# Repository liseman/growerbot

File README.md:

# Growerbot

Welcome to the Growerbot github repository. The growerbot is a social gardening assistant, more details at [growerbot.com](http://www.growerbot.com/)

## Arduino source 

To use the Arduino source you'll need those three libraries :

* [Time Library](http://www.arduino.cc/playground/uploads/Code/Time.zip)
* [Adafruits Lux sensor library](https://github.com/adafruit/TSL2561-Arduino-Library)
* [Adafruits DHT sensor library](https://github.com/adafruit/DHT-sensor-library)

Download them and put them into the libraries folder of your Aduino IDE installation.

To install Arduino IDE please go to : [http://arduino.cc/en/Main/Software](http://arduino.cc/en/Main/Software)

To upload the program into the Growerbot please follow the instruction on the fifth video of the [assembly videos](http://www.growerbot.com/2013/02/03/growerbot-kit-assembly-videos/).

### Linux Users

If you have installed Arduino IDE via an installer (i.e. apt-get) note that your library may be in your home folder at ~/sketchbook/libraries (Tested only with Ubuntu).
Also if you have problems compiling the Time library and it's the Time/DateString.cpp file that cause the problem you can remove all the "PROGMEM" keywords to make it compile without problems.

## Electric Imp Source

Those file are samples to use with the Electrc Imp SD card. Please refer to the Readme file into the folder for more help.

## PCBs

Those are the schematics and board design to build a Growerbot, you can also buy a kit at [www.growerbot.com/buy/](http://www.growerbot.com/buy/).

To learn what you need and how to build your Growerbot please watch the assembly videos at [www.growerbot.com/blog/](http://www.growerbot.com/2013/02/03/growerbot-kit-assembly-videos/)

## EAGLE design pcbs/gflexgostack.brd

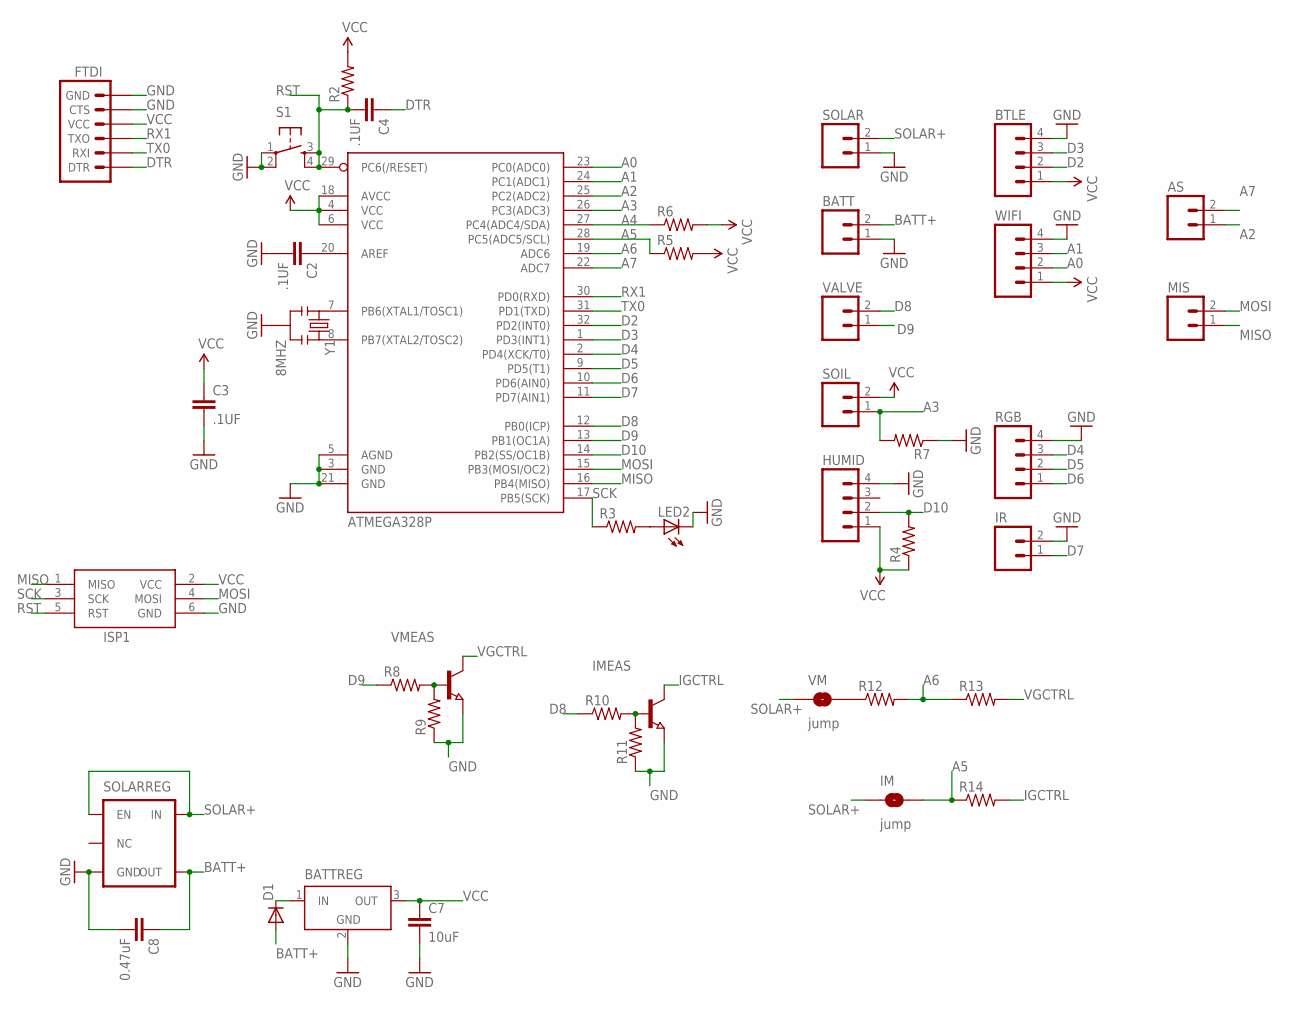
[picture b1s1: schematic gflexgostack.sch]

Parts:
AS: M02PTH; 1X02; DIGI PPTC021LFBN-RC
ATMEGA328P: ATMEGA168; TQFP32-08; DIGI ATMEGA328P-AU
BATT: M02PTH; 1X02; DIGI PPTC021LFBN-RC
BATTREG: LT1129CST5; SOT223; MPN LT1129CST-3.3#PBF-ND; DIGI MCP1826S-3302E/DB
BTLE: M04PTH; 1X04; DIGI PPTC041LFBN-RC
C2, C3, C4: .1UF; 0402-CAP; DIGI GRM155R71C104KA88D
C7: 10uF; 0402-CAP; DIGI AMK105CBJ106MV-F
C8: 0.47uF; 0402-CAP; DIGI GRM155R61A474KE15D
D1: DIODESMA; SMA-DIODE; DIGI B340A-13-F
FTDI: ARDUINO_SERIAL_PROGRAMPTH; 1X06; DIGI PPTC061LFBN-RC
HUMID: M04PTH; 1X04; DIGI PPTC041LFBN-RC
IM: jump; SJ_2S-TRACE
IMEAS: NPN-TRANSISTOR_SOT23; SOT23
IR: M02PTH; 1X02; DIGI PPTC021LFBN-RC
ISP1: AVRISP-6; AVRISP; DIGI 961206-6404-AR
LED2: LED0603; LED-0603; DIGI TLMG1100-GS08
MIS: M02PTH; 1X02; DIGI PPTC021LFBN-RC
R2, R4, R5, R6, R7: RESISTOR0603-RES; 0603-RES; DIGI ERJ-3GEYJ103V
R3: RESISTOR0603-RES; 0603-RES; DIGI ERJ-3GEYJ331V
R8, R10: RESISTOR0603-RES; 0603-RES; DIGI ERJ-3GEYJ431V
R9, R11: RESISTOR0603-RES; 0603-RES; DIGI ERJ-3GEYJ432V
R12: RESISTOR0603-RES; 0603-RES; DIGI ERJ-3GEYJ202V
R13: RESISTOR0603-RES; 0603-RES; DIGI ERJ-3GEYJ102V
R14: RESISTOR0603-RES; 0603-RES; DIGI ERJ-3RSJR10V
RGB: M04PTH; 1X04; DIGI PPTC041LFBN-RC
S1: TAC_SWITCHSMD; TACTILE_SWITCH_SMD; DIGI RS-187R05A2-DS MT RT
SOIL: M02PTH; 1X02; DIGI PPTC021LFBN-RC
SOLAR: M02PTH; 1X02; DIGI PPTC021LFBN-RC
SOLARREG: V_REG_MIC52195V; SOT23-5; DIGI MIC5213-5.0YC5 TR
VALVE: M02PTH; 1X02; DIGI PPTC021LFBN-RC
VM: jump; SJ_2S-TRACE
VMEAS: NPN-TRANSISTOR_SOT23; SOT23
WIFI: M04PTH; 1X04; DIGI PPTC041LFBN-RC
Y1: 8MHZ; RESONATOR-SMD; DIGI PRQV8.00CR5010Y000

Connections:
A0: ATMEGA328P.23 (PC0(ADC0)), WIFI.2
A1: ATMEGA328P.24 (PC1(ADC1)), WIFI.3
A2: AS.1, ATMEGA328P.25 (PC2(ADC2))
A3: ATMEGA328P.26 (PC3(ADC3)), R7.2, SOIL.1
A4: ATMEGA328P.27 (PC4(ADC4/SDA)), R6.1
A5: ATMEGA328P.28 (PC5(ADC5/SCL)), IM.2, R5.1, R14.1
A6: ATMEGA328P.19 (ADC6), R12.2, R13.1
A7: AS.2, ATMEGA328P.22 (ADC7)
BATT+: BATT.2, C8.1, D1.A, SOLARREG.4 (OUT)
D2: ATMEGA328P.32 (PD2(INT0)), BTLE.2
D3: ATMEGA328P.1 (PD3(INT1)), BTLE.3
D4: ATMEGA328P.2 (PD4(XCK/T0)), RGB.3
D5: ATMEGA328P.9 (PD5(T1)), RGB.2
D6: ATMEGA328P.10 (PD6(AIN0)), RGB.1
D7: ATMEGA328P.11 (PD7(AIN1)), IR.1
D8: ATMEGA328P.12 (PB0(ICP)), R10.1, VALVE.2
D9: ATMEGA328P.13 (PB1(OC1A)), R8.1, VALVE.1
D10: ATMEGA328P.14 (PB2(SS/OC1B)), HUMID.2, R4.2
DTR: C4.1, FTDI.1 (DTR)
GND: ATMEGA328P.3 (GND), ATMEGA328P.5 (AGND), ATMEGA328P.21 (GND), BATT.1, BATTREG.2 (GND), BATTREG.4 (GND), BTLE.4, C2.2, C3.2, C7.2, C8.2, FTDI.5 (CTS), FTDI.6 (GND), HUMID.4, IMEAS.2 (E), IR.2, ISP1.6 (GND), LED2.C, R7.1, R9.1, R11.1, RGB.4, S1.1, S1.2, SOLAR.1, SOLARREG.3 (GND), VMEAS.2 (E), WIFI.4, Y1.2
IGCTRL: IMEAS.3 (C), R14.2
MISO: ATMEGA328P.16 (PB4(MISO)), ISP1.1 (MISO), MIS.1
MOSI: ATMEGA328P.15 (PB3(MOSI/OC2)), ISP1.4 (MOSI), MIS.2
unnamed: ATMEGA328P.8 (PB7(XTAL2/TOSC2)), Y1.3
unnamed: ATMEGA328P.7 (PB6(XTAL1/TOSC1)), Y1.1
unnamed: R8.2, R9.2, VMEAS.1 (B)
unnamed: ATMEGA328P.20 (AREF), C2.1
unnamed: LED2.A, R3.2
unnamed: IMEAS.1 (B), R10.2, R11.2
unnamed: R12.1, VM.2
unnamed: BATTREG.1 (IN), D1.C
RST: ATMEGA328P.29 (PC6(/RESET)), C4.2, ISP1.5 (RST), R2.1, S1.3, S1.4
RX1: ATMEGA328P.30 (PD0(RXD)), FTDI.3 (TXO)
SCK: ATMEGA328P.17 (PB5(SCK)), ISP1.3 (SCK), R3.1
SOLAR+: IM.1, SOLAR.2, SOLARREG.1 (EN), SOLARREG.5 (IN), VM.1
TX0: ATMEGA328P.31 (PD1(TXD)), FTDI.2 (RXI)
VCC: ATMEGA328P.4 (VCC), ATMEGA328P.6 (VCC), ATMEGA328P.18 (AVCC), BATTREG.3 (OUT), BTLE.1, C3.1, C7.1, FTDI.4 (VCC), HUMID.1, ISP1.2 (VCC), R2.2, R4.1, R5.2, R6.2, SOIL.2, WIFI.1
VGCTRL: R13.2, VMEAS.3 (C)

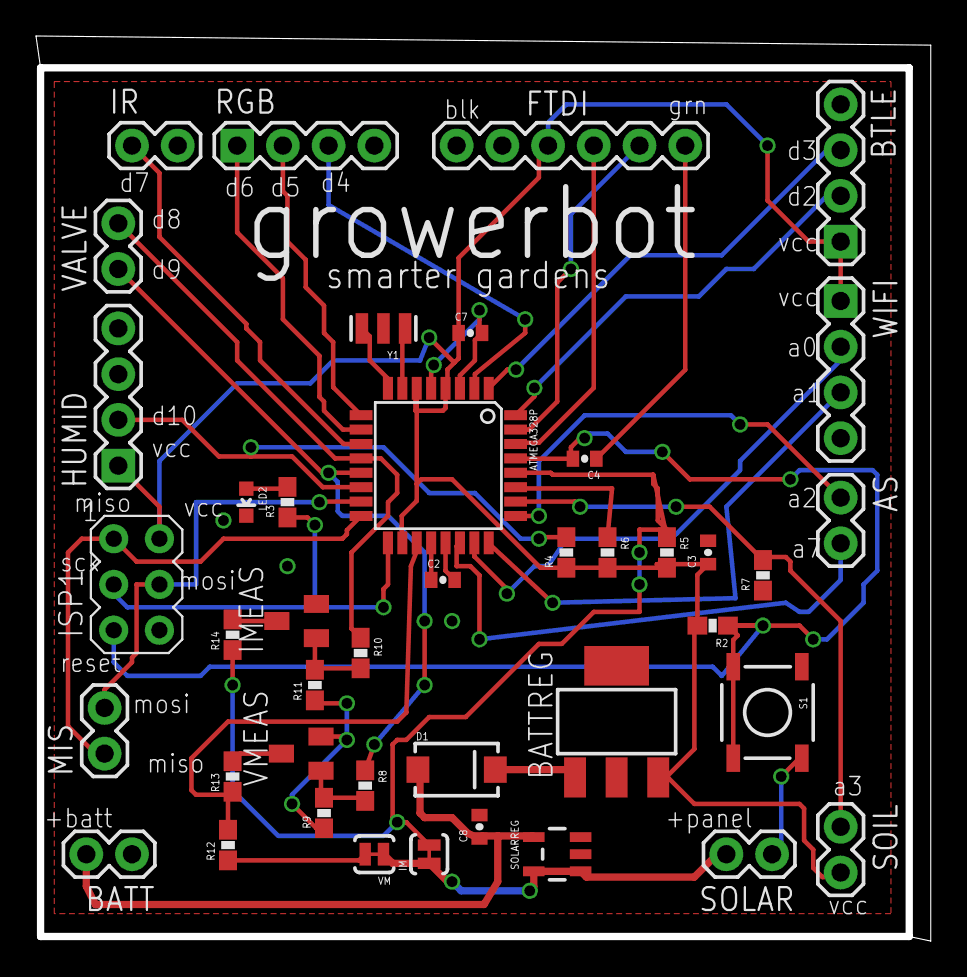
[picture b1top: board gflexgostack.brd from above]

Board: 4 copper layers, 49.3 x 49.9 mm, 43 parts (0 on the bottom side), 38 nets.

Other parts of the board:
U$1: GLOGO

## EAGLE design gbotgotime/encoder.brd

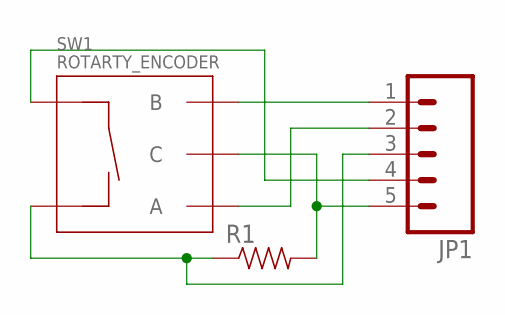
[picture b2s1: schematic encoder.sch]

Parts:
JP1: M05PTH; 1X05
R1: RESISTORPTH-1/4W; AXIAL-0.4
SW1: ROTARTY_ENCODER; ROTARY_ENC_PLAIN

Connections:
unnamed: JP1.1, SW1.B
unnamed: JP1.2, SW1.A
unnamed: JP1.5, R1.P$2 (2), SW1.C
unnamed: JP1.3, R1.P$1 (1), SW1.SW-
unnamed: JP1.4, SW1.SW+

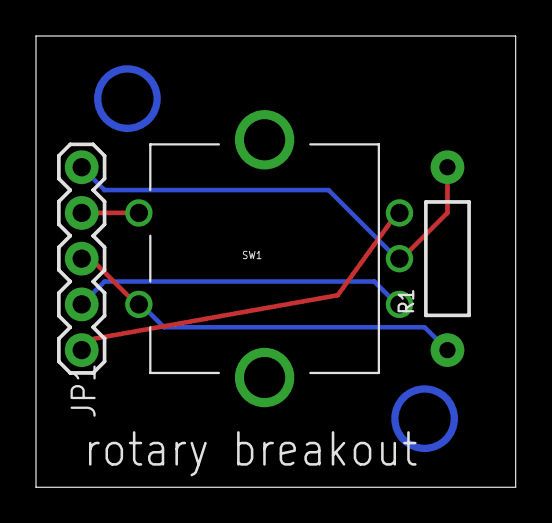
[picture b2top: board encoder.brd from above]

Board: 2 copper layers, 26.6 x 25.1 mm, 3 parts (0 on the bottom side), 5 nets.

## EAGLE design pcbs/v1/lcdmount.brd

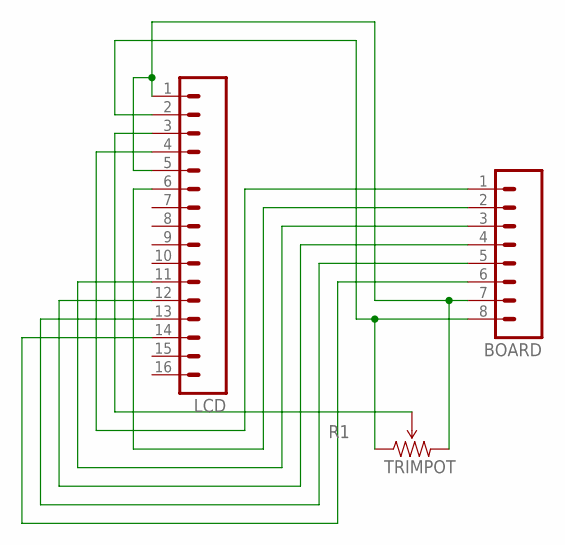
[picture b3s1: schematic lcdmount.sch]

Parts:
BOARD: M081X08; 1X08
LCD: M16PTH; 1X16
R1: TRIMPOT; 3362U-2

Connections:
unnamed: BOARD.7, LCD.1, LCD.5, R1.3 (CW)
unnamed: BOARD.8, LCD.2, R1.1 (CCW)
unnamed: LCD.3, R1.2 (WIPER)
unnamed: BOARD.1, LCD.4
unnamed: BOARD.3, LCD.11
unnamed: BOARD.2, LCD.6
unnamed: BOARD.4, LCD.12
unnamed: BOARD.5, LCD.13
unnamed: BOARD.6, LCD.14

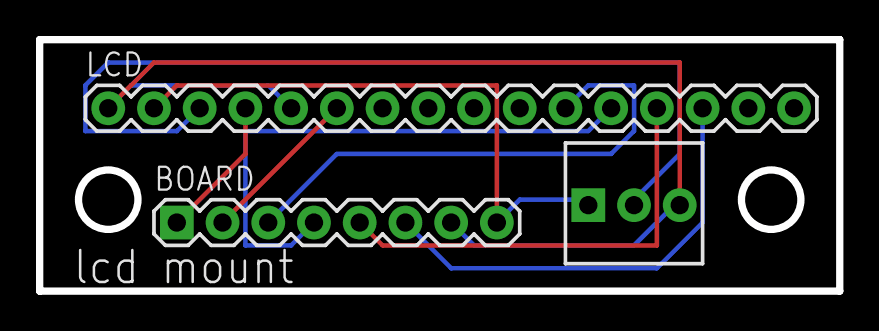
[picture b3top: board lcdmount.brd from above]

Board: 2 copper layers, 44.5 x 14.0 mm, 3 parts (0 on the bottom side), 9 nets.

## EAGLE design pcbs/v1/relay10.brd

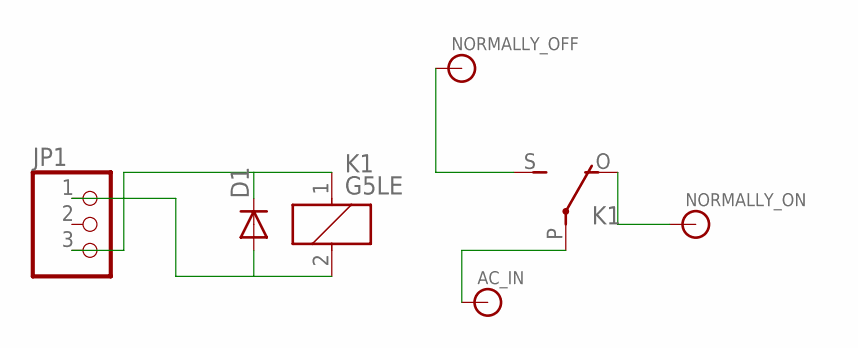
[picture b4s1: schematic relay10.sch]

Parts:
AC_IN: BANANA_CONN
D1: 1N4004; DO41-10
JP1: PINHD-1X3; 1X03
K1: G5LE
NORMALLY_OFF: BANANA_CONN
NORMALLY_ON: BANANA_CONN

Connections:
unnamed: D1.A, JP1.1, K1.2
unnamed: D1.C, JP1.3, K1.1
unnamed: K1.S, NORMALLY_OFF.P$1
unnamed: K1.O, NORMALLY_ON.P$1
unnamed: AC_IN.P$1, K1.P

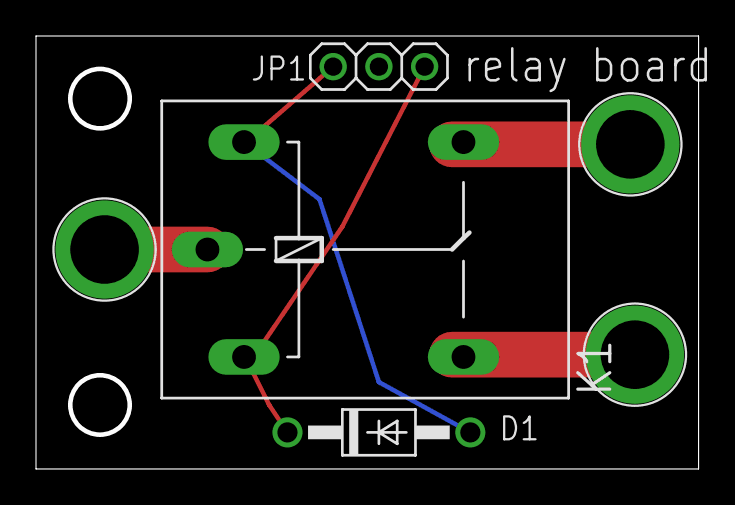
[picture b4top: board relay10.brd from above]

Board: 2 copper layers, 36.6 x 23.8 mm, 6 parts (0 on the bottom side), 5 nets.

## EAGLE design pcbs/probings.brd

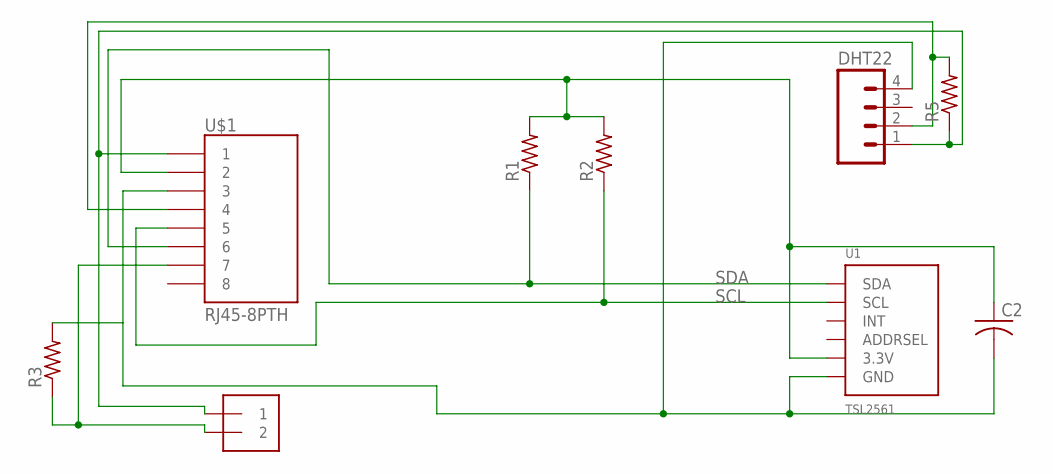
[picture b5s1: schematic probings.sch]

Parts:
C2: C-US025-024X044; C025-024X044
DHT22: M04PTH; 1X04
J1: 1X2-3.5MM
R1, R2, R3, R5: R-US_0204/7; 0204/7
U1: TSL2561; TSL2561_FN
U$1: RJ45-8PTH; RJ45-8

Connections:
unnamed: C2.1, R1.2, R2.2, U1.VDD (3.3V), U$1.2
unnamed: C2.2, DHT22.4, R3.2, U1.VSS (GND), U$1.3
unnamed: DHT22.1, J1.1, R5.1, U$1.1
unnamed: DHT22.2, R5.2, U$1.4
unnamed: J1.2, R3.1, U$1.7
SCL: R2.1, U1.CLK (SCL), U$1.5
SDA: R1.1, U1.DATA (SDA), U$1.6

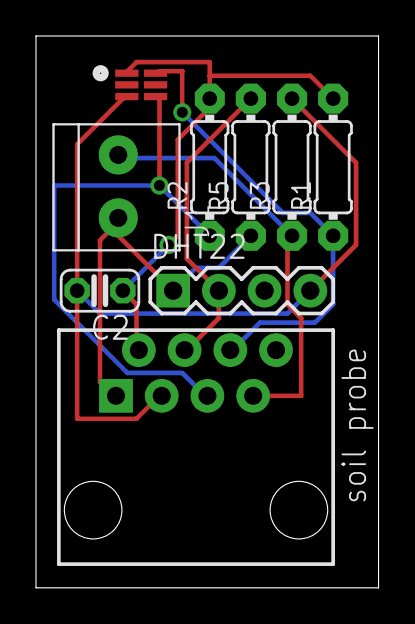
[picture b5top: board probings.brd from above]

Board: 2 copper layers, 19.0 x 30.7 mm, 9 parts (0 on the bottom side), 7 nets.

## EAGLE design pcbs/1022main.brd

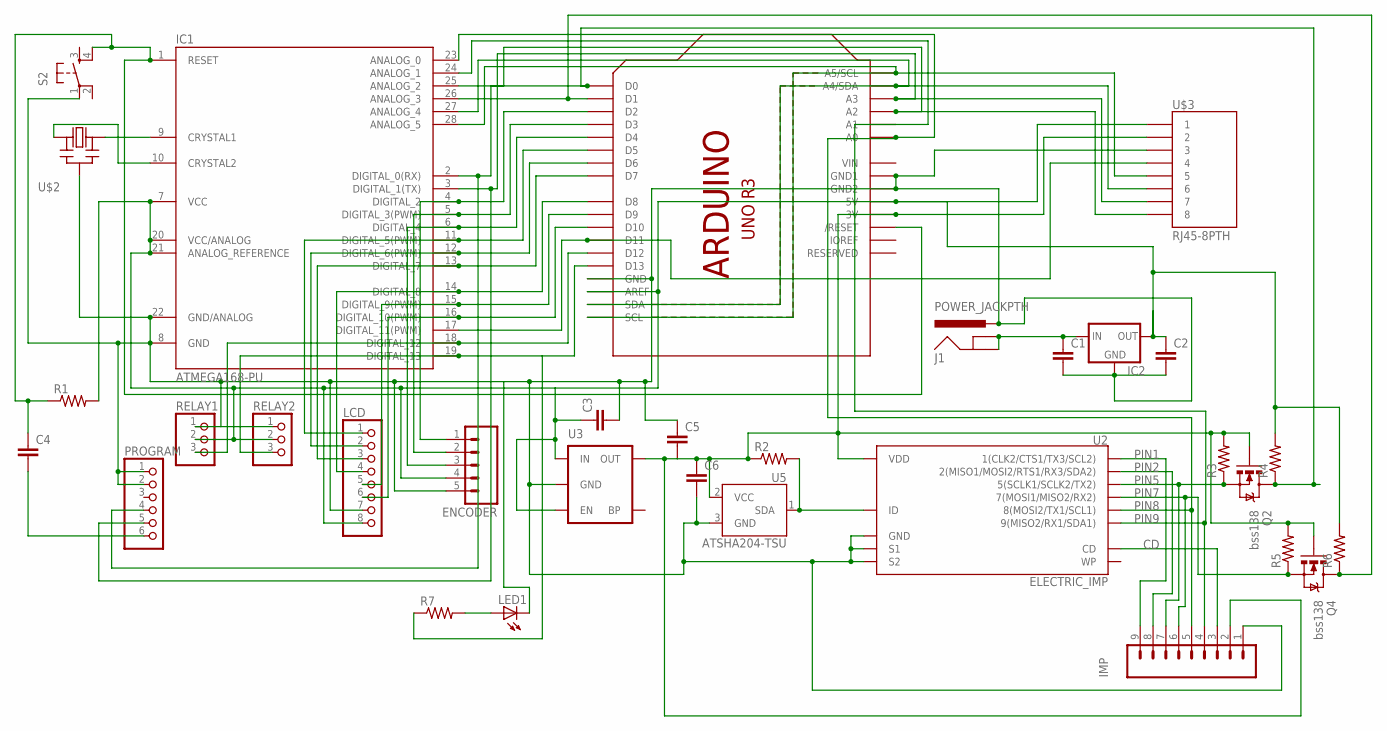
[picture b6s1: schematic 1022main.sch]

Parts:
C1, C2, C3, C4, C5, C6: CAPPTH; CAP-PTH-SMALL
ENCODER: M05PTH; 1X05
IC1: ATMEGA168-PU; DIL28-3
IC2: V_REG_78XX-TO-220; TO-220-ALT
IMP: M09; 1X09
J1: POWER_JACKPTH; POWER_JACK_PTH
LCD: PINHD-1X8CLEANBIG; 1X08-CLEANBIG
LED1: LED3MM
PROGRAM: PINHD-1X6; 1X06
Q2, Q4: bss138; SOT23-3
R1, R2, R3, R4, R5, R6, R7: R-US_0204/7; 0204/7
RELAY1, RELAY2: PINHD-1X3; 1X03
S2: TAC_SWITCHPTH; TACTILE-PTH
U1: ARDUINOR3-DIMENSION; ARDUINOR3
U2: ELECTRIC_IMP; SD_MMC_SOCKET
U3: V_REG_MIC52193.3V; SOT23-5
U5: ATSHA204-TSU; SOT23-3
U$2: CERMOSCILL-THM; CERM_OSC
U$3: RJ45-8PTH; RJ45-8

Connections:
3.3V: C5.2, C6.1, IMP.2, Q2.1 (G), Q4.1 (G), R2.1, R3.2, R5.2, U1.3V, U2.4 (VDD), U3.5 (OUT), U5.2 (VCC), U$3.2
CD: IMP.3, U2.CD
GND: C1.2, C2.2, C3.2, C5.1, C6.2, ENCODER.5, IC1.8 (GND), IC1.22 (GND/ANALOG), IC2.GND, IMP.1, J1.PWR, LCD.7, LED1.K (C), PROGRAM.1, PROGRAM.2, RELAY1.1, RELAY2.1, S2.1, U1.GND, U1.GND1, U1.GND2, U2.3 (GND), U2.S1, U2.S2, U3.2 (GND), U5.3 (GND), U$2.P$2 (GND), U$3.3
unnamed: IC1.19 (DIGITAL_13), R7.1, RELAY2.3, U1.D13
unnamed: IC1.18 (DIGITAL_12), RELAY1.3, U1.D12
unnamed: IC1.17 (DIGITAL_11(PWM)), U1.D11, U$3.4
unnamed: IC1.16 (DIGITAL_10(PWM)), LCD.6, U1.D10
unnamed: IC1.15 (DIGITAL_9(PWM)), LCD.5, U1.D9
unnamed: IC1.14 (DIGITAL_8), LCD.4, U1.D8
unnamed: IC1.13 (DIGITAL_7), LCD.3, U1.D7
unnamed: IC1.12 (DIGITAL_6(PWM)), LCD.2, U1.D6
unnamed: IC1.11 (DIGITAL_5(PWM)), LCD.1, U1.D5
unnamed: ENCODER.3, IC1.6 (DIGITAL_4), U1.D4
unnamed: ENCODER.2, IC1.5 (DIGITAL_3(PWM)), U1.D3
unnamed: ENCODER.1, IC1.4 (DIGITAL_2), U1.D2
unnamed: IC1.3 (DIGITAL_1(TX)), PROGRAM.5, Q4.3 (D), R6.1, U1.D1
unnamed: IC1.2 (DIGITAL_0(RX)), PROGRAM.4, Q2.3 (D), R4.1, U1.D0
unnamed: IC1.27 (ANALOG_4), U1.A4 (A4/SDA), U1.SDA, U$3.6
unnamed: IC1.28 (ANALOG_5), U1.A5 (A5/SCL), U1.SCL, U$3.5
unnamed: LED1.A, R7.2
unnamed: IC1.25 (ANALOG_2), U1.A2, U$3.8
unnamed: IC1.26 (ANALOG_3), U1.A3, U$3.7
unnamed: R2.2, U2.6 (ID), U5.1 (SDA)
unnamed: C1.1, IC2.IN, J1.GND, J1.GNDBREAK
unnamed: C4.2, PROGRAM.6
unnamed: IC1.9 (CRYSTAL1), U$2.P$3 (OUT)
unnamed: IC1.10 (CRYSTAL2), U$2.P$1 (IN)
unnamed: C2.1, C3.1, ENCODER.4, IC1.7 (VCC), IC1.20 (VCC/ANALOG), IC1.21 (ANALOG_REFERENCE), IC2.OUT, LCD.8, R1.2, R4.2, R6.2, RELAY1.2, RELAY2.2, U1.5V, U1.AREF, U3.1 (IN), U3.3 (EN), U$3.1
PIN1: IMP.9, U2.1 (1(CLK2/CTS1/TX3/SCL2))
PIN2: IMP.8, U2.2 (2(MISO1/MOSI2/RTS1/RX3/SDA2))
PIN5: IMP.7, Q2.2 (S), R3.1, U2.5 (5(SCLK1/SCLK2/TX2))
PIN7: IMP.6, Q4.2 (S), R5.1, U2.7 (7(MOSI1/MISO2/RX2))
PIN8: IC1.23 (ANALOG_0), IMP.5, U1.A0, U2.8 (8(MOSI2/TX1/SCL1))
PIN9: IC1.24 (ANALOG_1), IMP.4, U1.A1, U2.9 (9(MISO2/RX1/SDA1))
RELAY1: C4.1, IC1.1 (RESET), R1.1, S2.4, U1.RESET (/RESET)
VIN: U1.VIN

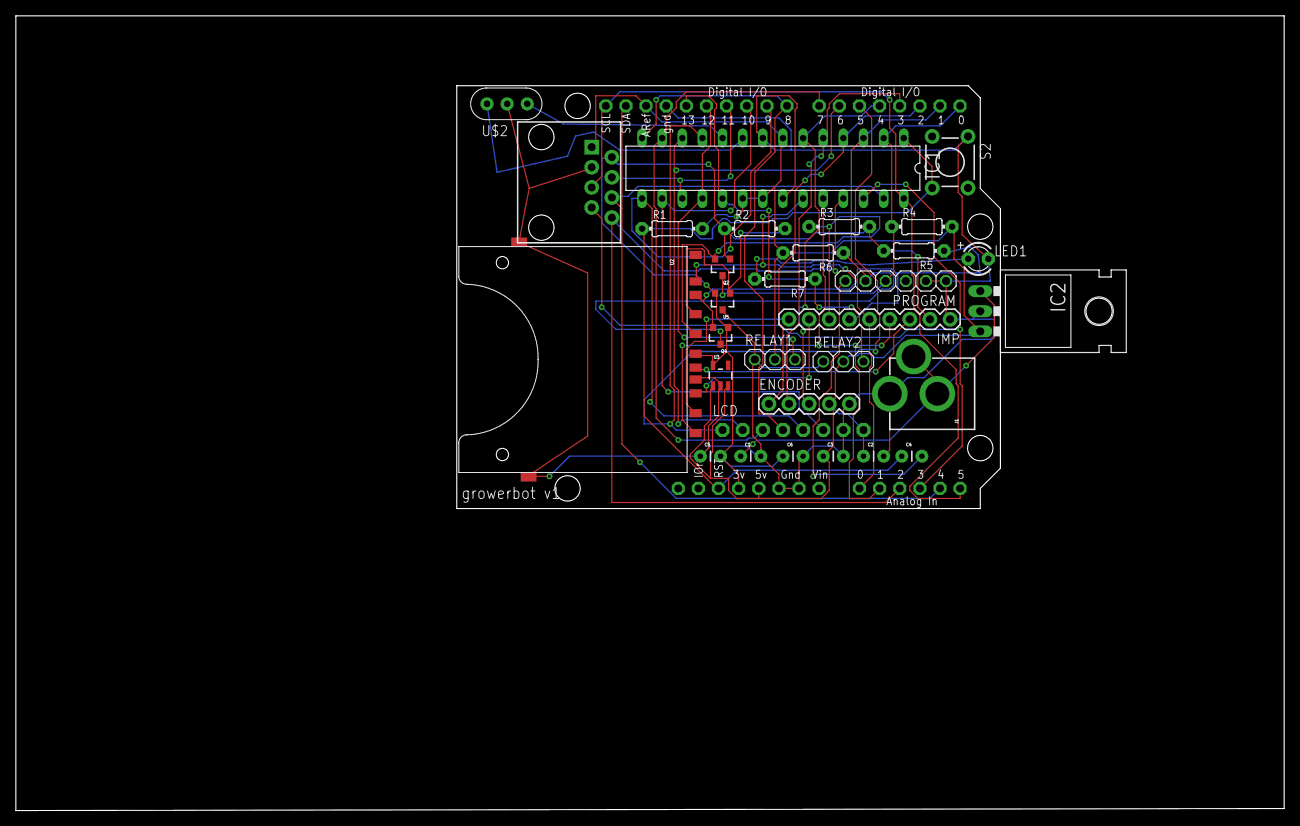
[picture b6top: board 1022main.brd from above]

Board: 2 copper layers, 160.0 x 100.3 mm, 32 parts (0 on the bottom side), 35 nets.

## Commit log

2012-12-18 growerbot source code, as shipped w/ kickstarters
2012-12-18 eagle source for kickstarter production boards
2013-01-06 fixed folder names, updated arduino code
2013-01-06 source code for electric imp, as shipped for kickstarter growerbots
2014-05-27 Ading demo for the new agent and device IDE on Electric Imp
2014-05-27 Small typo from french roots
2014-05-27 Let's be gentle with the node 60 seconds is enough
2014-05-28 Help for electric Imp
2014-05-28 Typos
2014-05-28 Adding documentation to the root Readme
2014-05-28 More infromation for programming the Growerbot and about the other Folders of the repository
2014-11-04 v1.5 test release
2014-12-08 updating all to v1.5
2015-01-07 v1.5

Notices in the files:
parts and their libraries:
SparkFun: Licensing: CC v3.0 Share-Alike You are welcome to use this library for commercial purposes.
